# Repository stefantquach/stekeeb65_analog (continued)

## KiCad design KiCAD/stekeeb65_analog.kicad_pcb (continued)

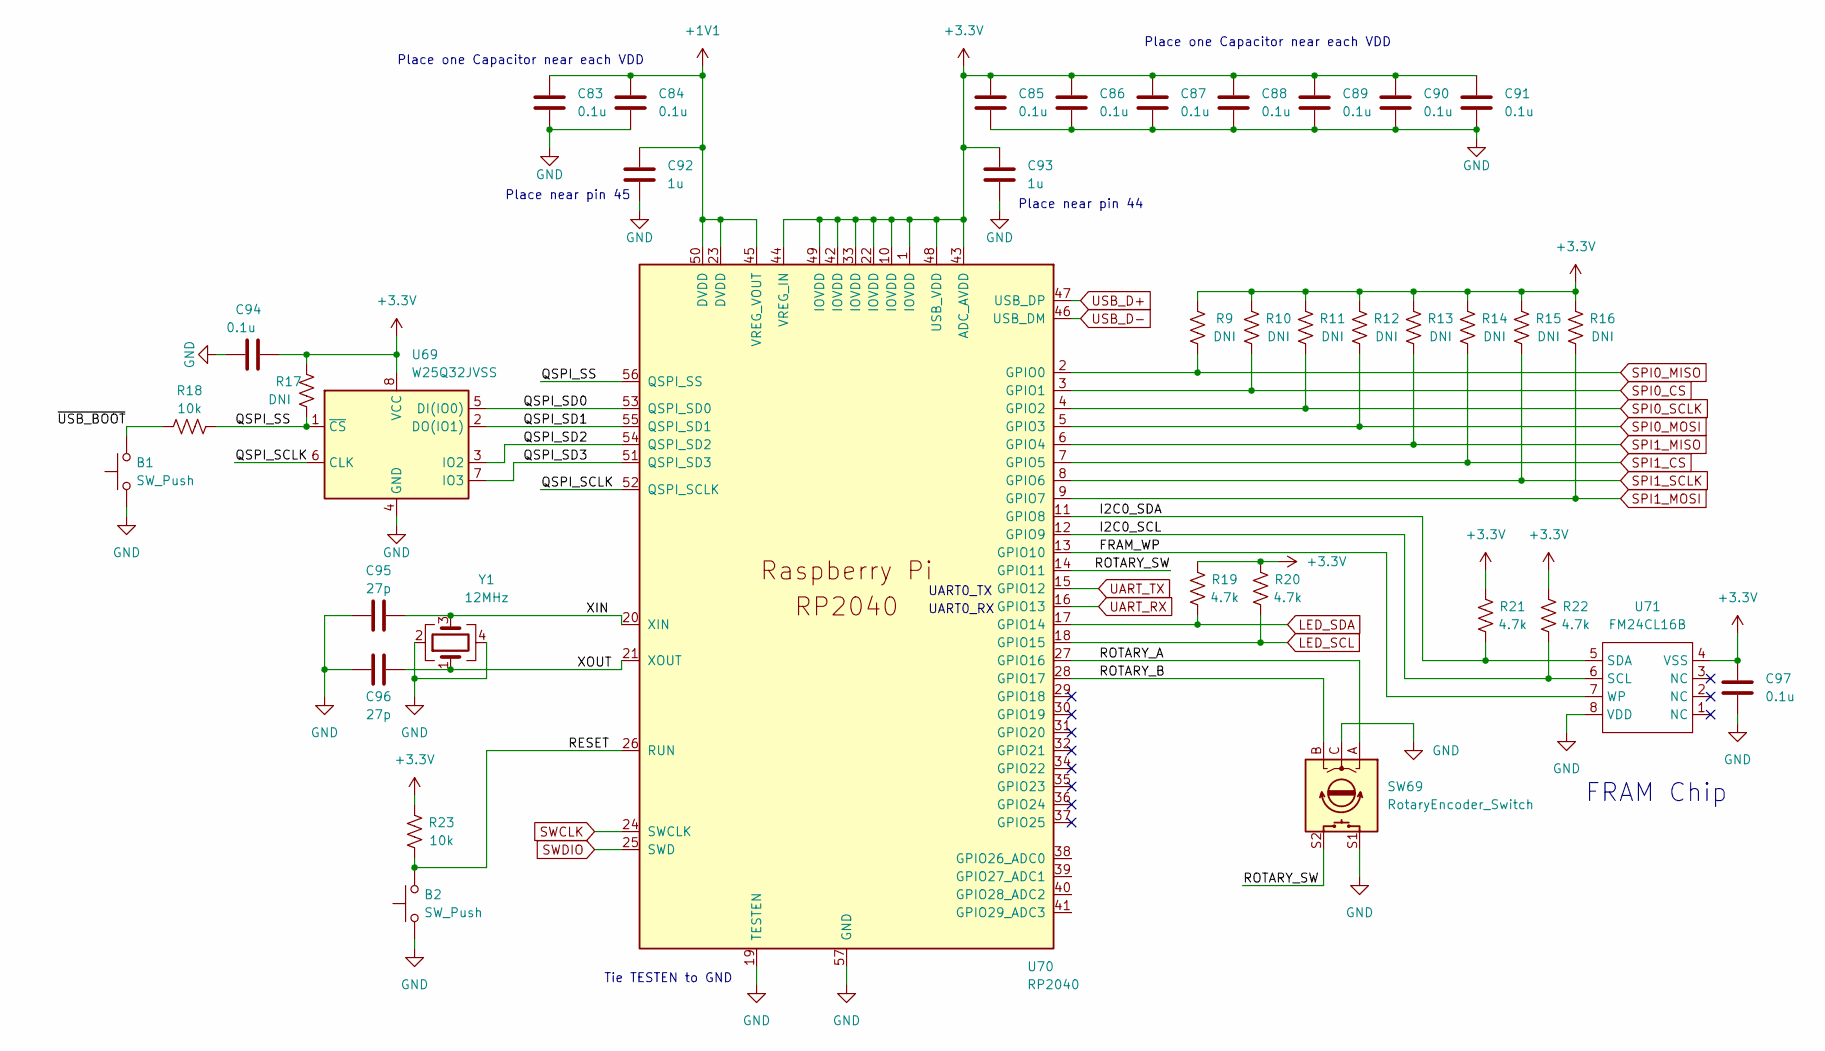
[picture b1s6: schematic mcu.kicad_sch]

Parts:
B1, B2: SW_Push; SKQG-1155865; Part Number MSLPT5252AG3TR
C83, C84, C85, C86, C87, C88, C89, C90, C91, C94, C97: 0.1u; C_0603_1608Metric_Pad1.08x0.95mm_HandSolder; Part Number C0603C104M4RAC7411
C92, C93: 1u; C_0603_1608Metric_Pad1.08x0.95mm_HandSolder; Part Number CL10B104KA8NNNC
C95, C96: 27p; C_0603_1608Metric_Pad1.08x0.95mm_HandSolder; Part Number C0603C270J3GAC7867
R9, R10, R11, R12, R13, R14, R15, R16, R17: DNI; R_0603_1608Metric_Pad0.98x0.95mm_HandSolder
R18, R23: 10k; R_0603_1608Metric_Pad0.98x0.95mm_HandSolder; Part Number RNCP0603FTD10K0
R19, R20, R21, R22: 4.7k; R_0603_1608Metric_Pad0.98x0.95mm_HandSolder
SW69: RotaryEncoder_Switch; RotaryEncoder_Alps_EC11E-Switch-Vertical-EDIT
U69: W25Q32JVSS; SOIC-8_5.23x5.23mm_P1.27mm; Part Number W25Q32JVSS
U70: RP2040; RP2040-QFN-56; Part Number SC0914(13)
U71: FM24CL16B; SOIC-8_3.9x4.9mm_P1.27mm
Y1: 12MHz; Crystal_SMD_3225-4Pin_3.2x2.5mm; Part Number RH100-12.000-18-2030-TR

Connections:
+1V1: C83.1, C84.1, C92.1, U70.23 (DVDD), U70.45 (VREG_VOUT), U70.50 (DVDD)
+3.3VA: C85.1, C86.1, C87.1, C88.1, C89.1, C90.1, C91.1, C93.1, C94.2, C97.1, R9.1, R10.1, R11.1, R12.1, R13.1, R14.1, R15.1, R16.1, R17.2, R19.1, R20.1, R21.1, R22.1, R23.1, U69.8 (VCC), U70.1 (IOVDD), U70.10 (IOVDD), U70.22 (IOVDD), U70.33 (IOVDD), U70.42 (IOVDD), U70.43 (ADC_AVDD), U70.44 (VREG_IN), U70.48 (USB_VDD), U70.49 (IOVDD), U71.4 (VSS); also elsewhere on the board
/MCU/FRAM_WP: U70.13 (GPIO10), U71.7 (WP)
/MCU/I2C0_SCL: R22.2, U70.12 (GPIO9), U71.6 (SCL)
/MCU/I2C0_SDA: R21.2, U70.11 (GPIO8), U71.5 (SDA)
/MCU/QSPI_SCLK: U69.6 (CLK), U70.52 (QSPI_SCLK)
/MCU/QSPI_SD0: U69.5 (DI(IO0)), U70.53 (QSPI_SD0)
/MCU/QSPI_SD1: U69.2 (DO(IO1)), U70.55 (QSPI_SD1)
/MCU/QSPI_SD2: U69.3 (IO2), U70.54 (QSPI_SD2)
/MCU/QSPI_SD3: U69.7 (IO3), U70.51 (QSPI_SD3)
/MCU/QSPI_SS: R17.1, R18.2, U69.1 (~CS), U70.56 (QSPI_SS)
/MCU/RESET: B2.2, R23.2, U70.26 (RUN)
/MCU/ROTARY_A: SW69.A, U70.27 (GPIO16)
/MCU/ROTARY_B: SW69.B, U70.28 (GPIO17)
/MCU/ROTARY_SW: SW69.S2, U70.14 (GPIO11)
/MCU/XIN: C95.2, U70.20 (XIN), Y1.3
/MCU/XOUT: C96.2, U70.21 (XOUT), Y1.1
/MCU/~USB_BOOT: B1.2, R18.1
GND: B1.1, B2.1, C83.2, C84.2, C85.2, C86.2, C87.2, C88.2, C89.2, C90.2, C91.2, C92.2, C93.2, C94.1, C95.1, C96.1, C97.2, SW69.C, SW69.S1, U69.4 (GND), U70.19 (TESTEN), U70.57 (GND), U71.8 (VDD), Y1.2, Y1.4; also elsewhere on the board
LED_SCL: R20.2, U70.18 (GPIO15); also elsewhere on the board
LED_SDA: R19.2, U70.17 (GPIO14); also elsewhere on the board
SPI0_CS: R10.2, U70.3 (GPIO1); also elsewhere on the board
SPI0_MISO: R9.2, U70.2 (GPIO0); also elsewhere on the board
SPI0_MOSI: R12.2, U70.5 (GPIO3); also elsewhere on the board
SPI0_SCLK: R11.2, U70.4 (GPIO2); also elsewhere on the board
SPI1_CS: R14.2, U70.7 (GPIO5); also elsewhere on the board
SPI1_MISO: R13.2, U70.6 (GPIO4); also elsewhere on the board
SPI1_MOSI: R16.2, U70.9 (GPIO7); also elsewhere on the board
SPI1_SCLK: R15.2, U70.8 (GPIO6); also elsewhere on the board
SWCLK: U70.24 (SWCLK); also elsewhere on the board
SWDIO: U70.25 (SWD); also elsewhere on the board
UART_RX: U70.16 (GPIO13); also elsewhere on the board
UART_TX: U70.15 (GPIO12); also elsewhere on the board
USB_D+: U70.47 (USB_DP); also elsewhere on the board
USB_D-: U70.46 (USB_DM); also elsewhere on the board

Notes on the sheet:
UART0_RX
Tie TESTEN to GND
Place near pin 45
FRAM Chip
Place one Capacitor near each VDD
Place near pin 44
UART0_TX

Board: 2 copper layers, 350 parts (281 on the bottom side), 137 nets, no tracks yet.

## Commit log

2023-06-24 Initial commit. WIP ADC page
2023-06-24 Interim commit before messing with files using script
2023-06-24 More interim commits
2023-06-24 Adding LED library
2023-06-24 Update references
2023-06-24 More script and schematic updates
2023-06-24 Adding missing led to layout
2023-06-25 Adding more footprints
2023-06-25 updated layout arrangement pre script
2023-06-25 Update interim layout before script
2023-06-25 I forgot to hit save before the last commit
2023-06-25 Kicad being weird
2023-06-25 Apply script to layout
2023-09-21 Update Lekker footprints to include non-1U sizes and stabilizers
2023-09-21 Fix right shift not having the 1.75U footprint
2023-10-29 Committing before changing to MUX design
2023-12-26 Finished initial routing of PCB
2024-08-28 pushing various updates
